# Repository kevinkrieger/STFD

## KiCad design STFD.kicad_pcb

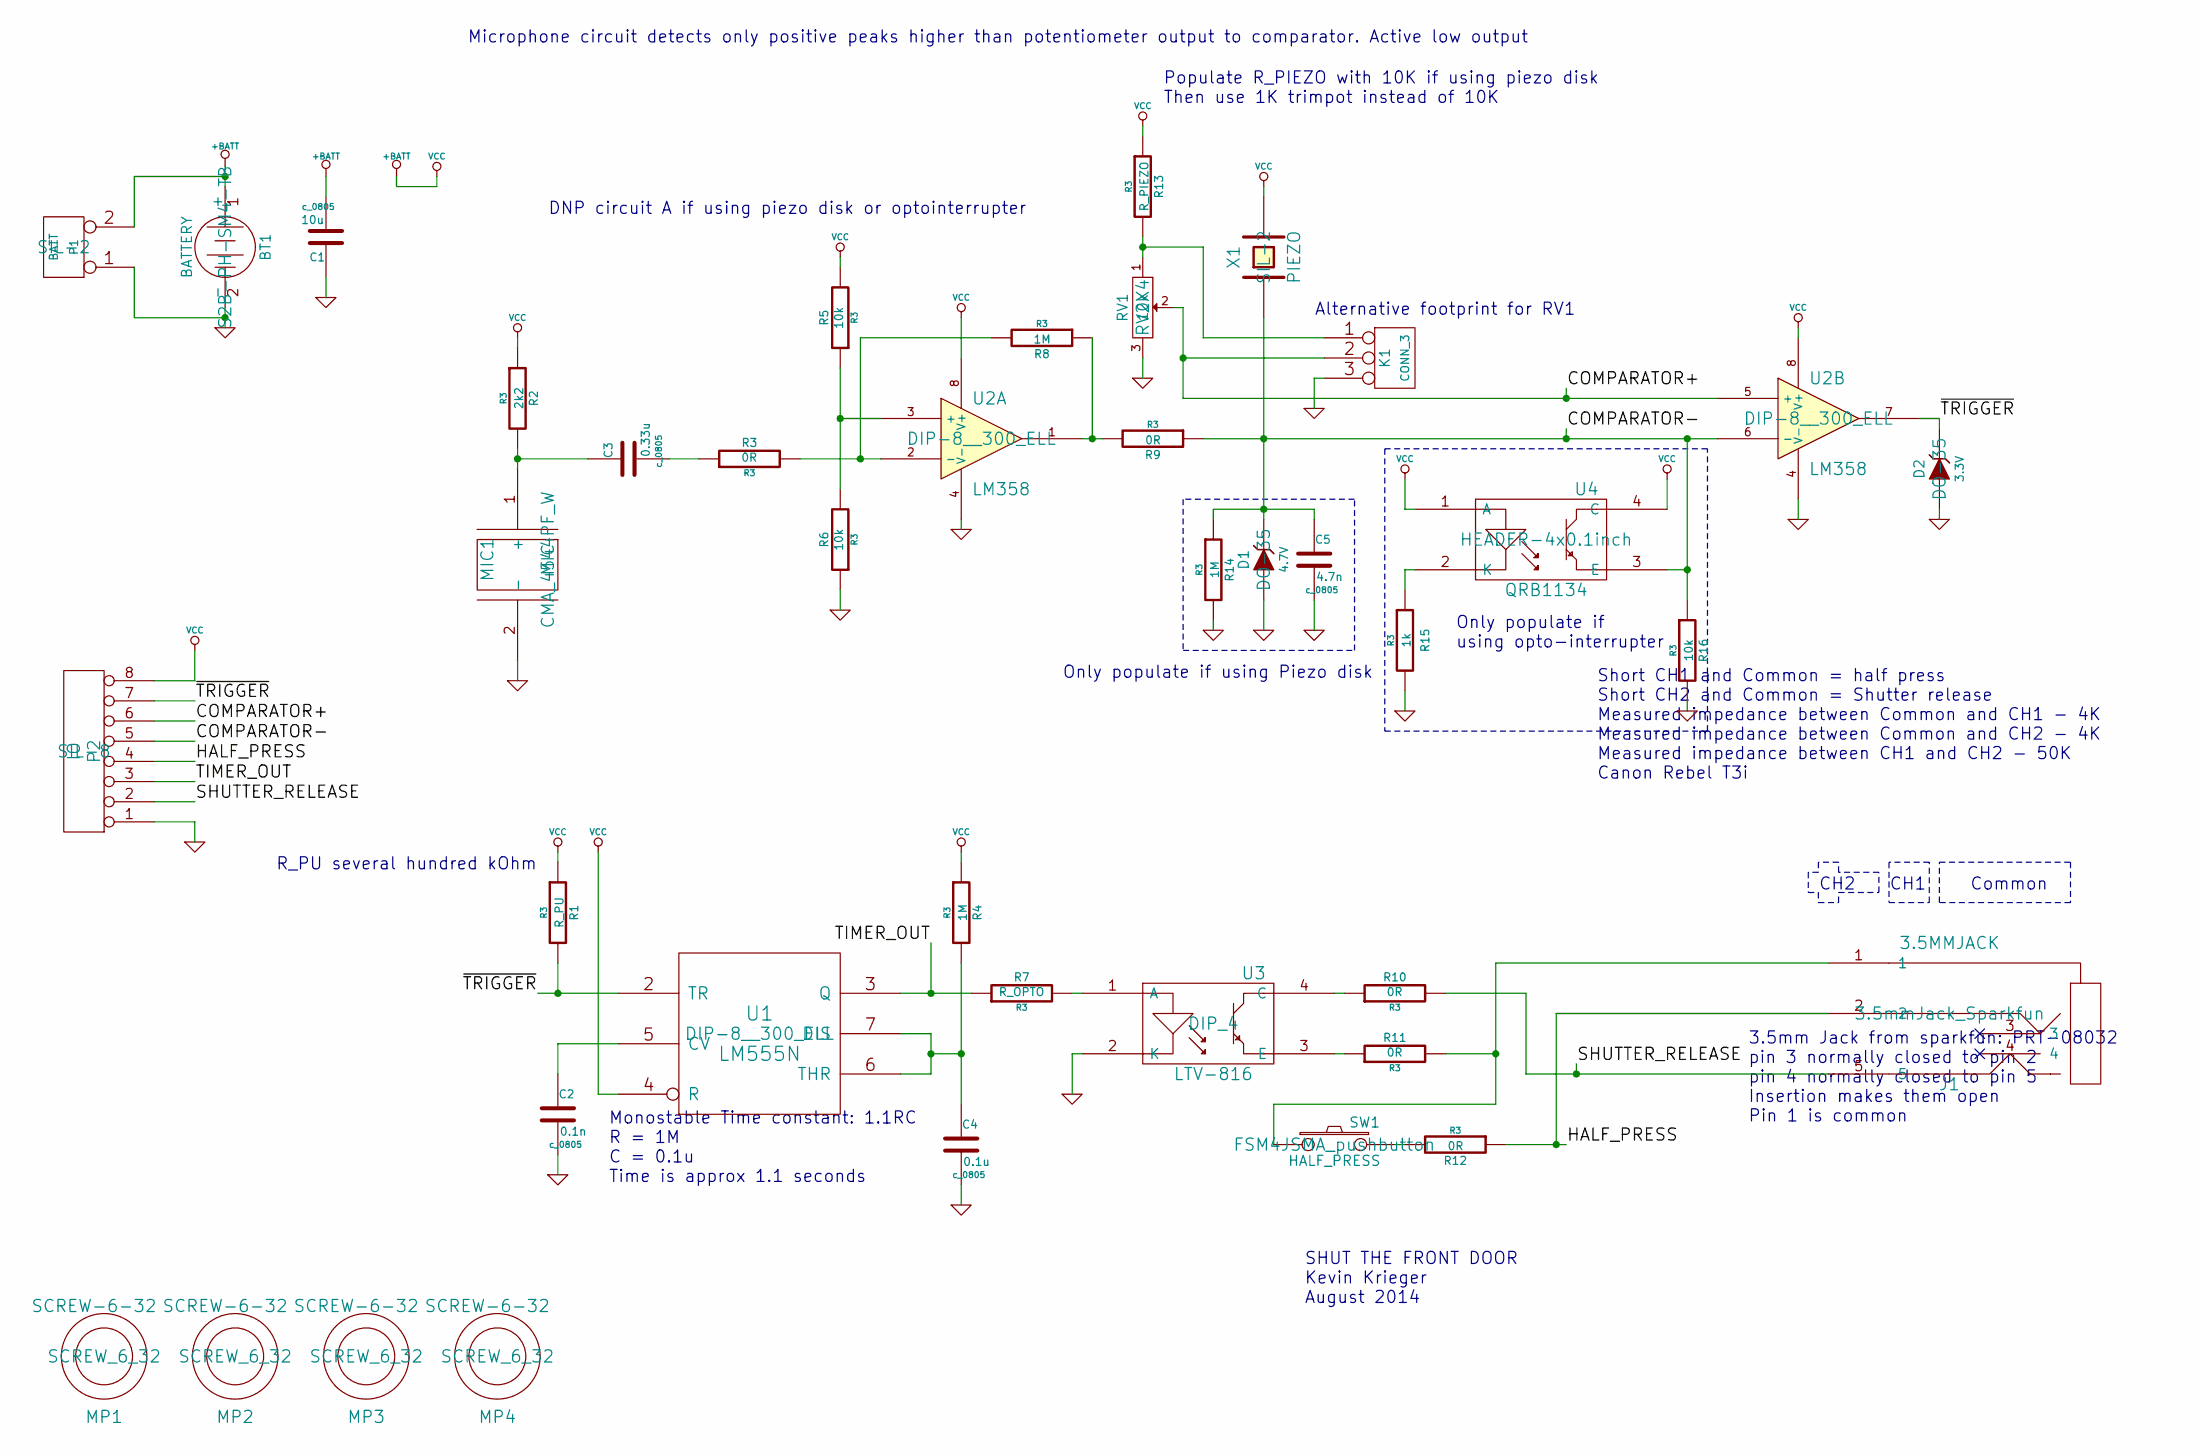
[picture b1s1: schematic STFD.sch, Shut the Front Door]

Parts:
BT1: BATTERY; S2B-PH-SM4-TB
C1: 10u; c_0805
C2: 0.1n; c_0805
C3: 0.33u; c_0805
C4: 0.1u; c_0805
C5: 4.7n; c_0805
D1: 4.7V; DO-35
D2: 3.3V; DO-35
J1: 3.5MMJACK; 3.5mmJack_Sparkfun
K1: CONN_3
MIC1: MIC; CMA_4544PF_W
MP1, MP2, MP3, MP4: SCREW-6-32; SCREW_6_32
P1: BATT; SIL-2
P2: IO; SIL-8
R1: R_PU; R3
R2: 2k2; R3
R3, R9, R10, R11, R12: 0R; R3
R4, R8, R14: 1M; R3
R5, R6, R16: 10k; R3
R7: R_OPTO; R3
R13: R_PIEZO; R3
R15: 1k; R3
RV1: 10k; RV2X4
SW1: HALF_PRESS; FSM4JSMA_pushbutton
U1: LM555N; DIP-8__300_ELL
U2: LM358; DIP-8__300_ELL
U3: LTV-816; DIP_4
U4: QRB1134; HEADER-4x0.1inch
X1: PIEZO; SIL-2

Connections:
+BATT: BT1.1 (+), C1.2, P1.2 (PM), P2.8, R1.1, R2.1, R4.1, R5.2, R13.1, U1.4 (R), U1.8 (VCC), U2.8 (V+), U4.1 (A), U4.4 (C), X1.2
/COMPARATOR+: K1.2 (PM), P2.6, RV1.2, U2.5 (+)
/COMPARATOR-: C5.1, D1.2 (K), P2.5, R9.1, R14.1, R16.1, U2.6 (-), U4.3 (E), X1.1
/HALF_PRESS: J1.2, P2.4, R12.1
/SHUTTER_RELEASE: J1.5, P2.2, R10.2
/TIMER_OUT: P2.3, R7.1, U1.3 (Q)
/~TRIGGER: D2.2 (K), P2.7, R1.2, U1.2 (TR), U2.7
GND: BT1.2 (-), C1.1, C2.2, C4.2, C5.2, D1.1 (A), D2.1 (A), K1.3, MIC1.2 (-), P1.1, P2.1, R6.1, R14.2, R15.2, R16.2, RV1.3, U1.1 (GND), U2.4 (V-), U3.2 (K)
unnamed: R5.1, R6.2, U2.3 (+)
unnamed: R8.1, R9.2, U2.1
unnamed: C4.1, R4.2, U1.6 (THR), U1.7 (DIS)
unnamed: C2.1, U1.5 (CV)
unnamed: R7.2, U3.1 (A)
unnamed: R3.2, R8.2, U2.2 (-)
unnamed: C3.2, R3.1
unnamed: C3.1, MIC1.1 (+), R2.2
unnamed: R15.1, U4.2 (K)
unnamed: K1.1, R13.2, RV1.1
unnamed: R12.2, SW1.2
unnamed: R10.1, U3.4 (C)
unnamed: R11.1, U3.3 (E)
unnamed: J1.1, R11.2, SW1.1

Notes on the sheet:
SHUT THE FRONT DOOR Kevin Krieger August 2014
Monostable Time constant: 1.1RC R = 1M C = 0.1u Time is approx 1.1 seconds
R_PU several hundred kOhm
Microphone circuit detects only positive peaks higher than potentiometer output to comparator. Active low output
3.5mm Jack from sparkfun: PRT-08032 pin 3 normally closed to pin 2 pin 4 normally closed to pin 5 Insertion makes them open Pin 1 is common
Common
CH1
CH2
Short CH1 and Common = half press Short CH2 and Common = Shutter release Measured impedance between Common and CH1 - 4K Measured impedance between Common and CH2 - 4K Measured impedance between CH1 and CH2 - 50K Canon Rebel T3i
Populate R_PIEZO with 10K if using piezo disk Then use 1K trimpot instead of 10K
Only populate if using Piezo disk
Only populate if using opto-interrupter
DNP circuit A if using piezo disk or optointerrupter
Alternative footprint for RV1

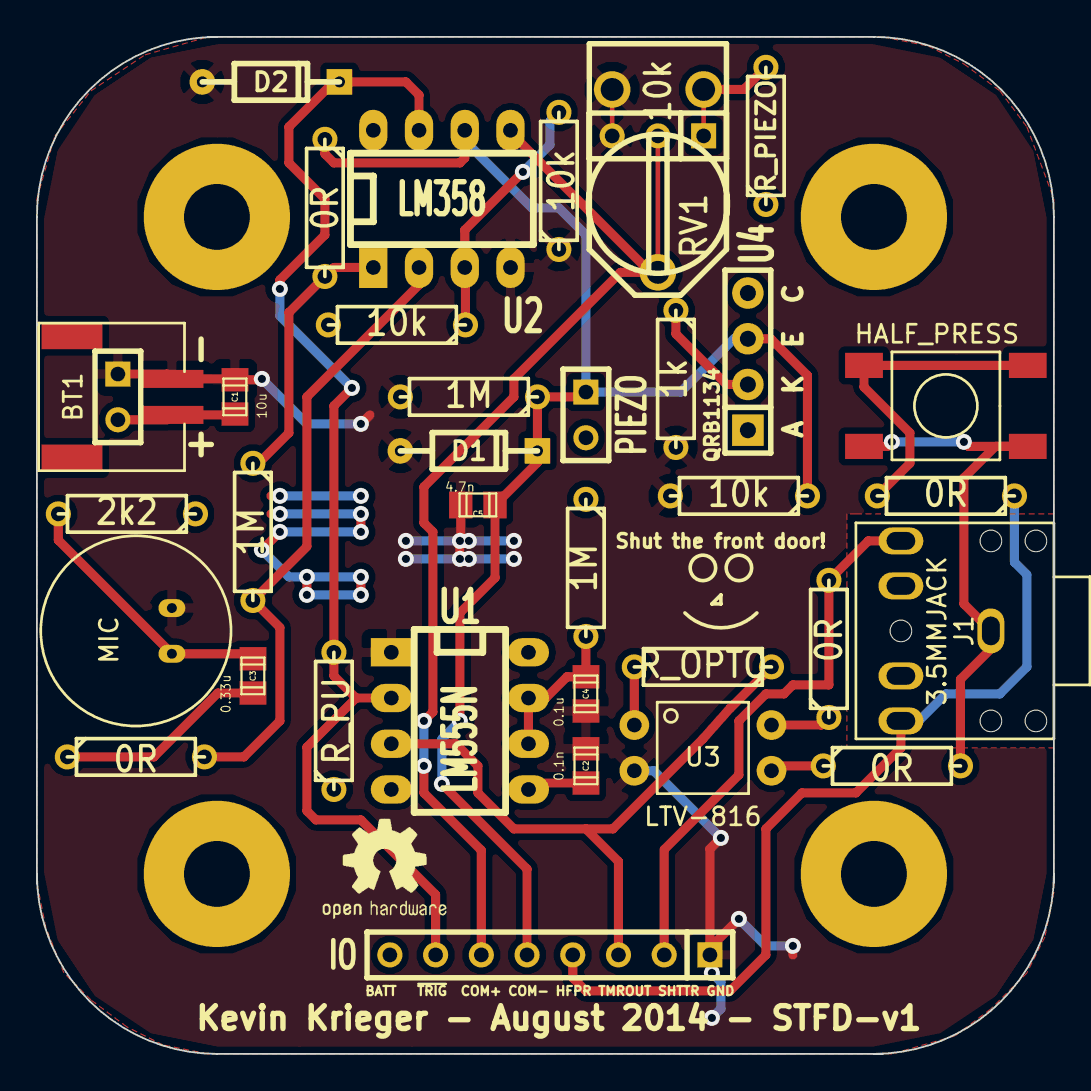
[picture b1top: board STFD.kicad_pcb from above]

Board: 2 copper layers, 56.5 x 56.5 mm, 40 parts (0 on the bottom side), 22 nets.

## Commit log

2014-08-25 Initial commit. CAD only
